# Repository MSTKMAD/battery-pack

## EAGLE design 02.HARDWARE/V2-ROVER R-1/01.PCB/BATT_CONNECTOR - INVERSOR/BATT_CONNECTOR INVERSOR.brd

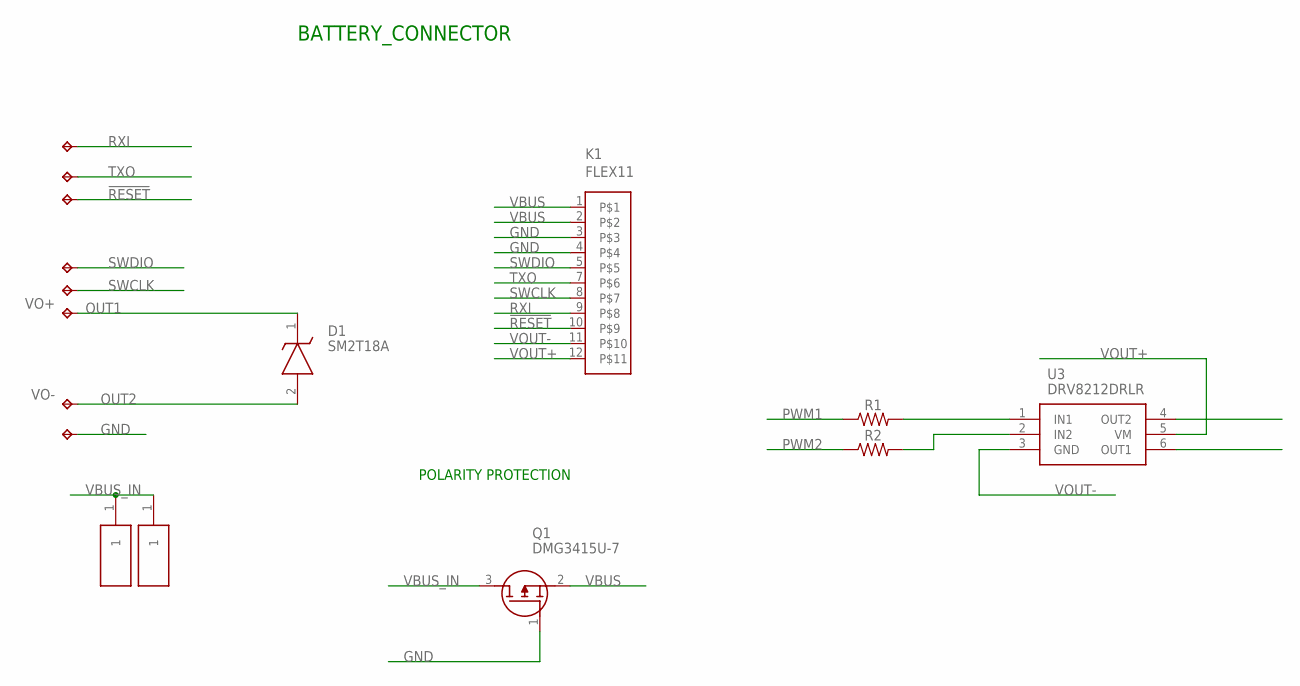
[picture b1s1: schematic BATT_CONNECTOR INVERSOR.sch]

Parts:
!RESET: TPB2,54; B2,54
D1: SM2T18A
GND: TPB2,54; B2,54
H1, H2: S1761-42R; S176142R
K1: FLEX11
Q1: DMG3415U-7; SSM3J332RLFT
R1, R2: 0805
RXI: TPB2,54; B2,54
SWCLK: TPB2,54; B2,54
SWDIO: TPB2,54; B2,54
TXO: TPB2,54; B2,54
U3: DRV8212DRLR; SOTFL50P160X60-6N
VO+: TPB2,54; B2,54
VO-: TPB2,54; B2,54

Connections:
!RESET: !RESET.TP, K1.10
GND: GND.TP, K1.3, K1.4, Q1.1 (G)
unnamed: R1.2, U3.1 (IN1)
unnamed: R2.2, U3.2 (IN2)
OUT1: D1.1 (K), U3.6 (OUT1), VO+.TP
OUT2: D1.2 (A), U3.4 (OUT2), VO-.TP
PWM1: R1.1
PWM2: R2.1
RXI: K1.9, RXI.TP
SWCLK: K1.8, SWCLK.TP
SWDIO: K1.5, SWDIO.TP
TXO: K1.7, TXO.TP
VBUS: K1.1, K1.2, Q1.2 (S)
VBUS_IN: H1.1, H2.1, Q1.3 (D)
VOUT+: K1.12, U3.5 (VM)
VOUT-: K1.11, U3.3 (GND)

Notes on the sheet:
POLARITY PROTECTION
BATTERY_CONNECTOR

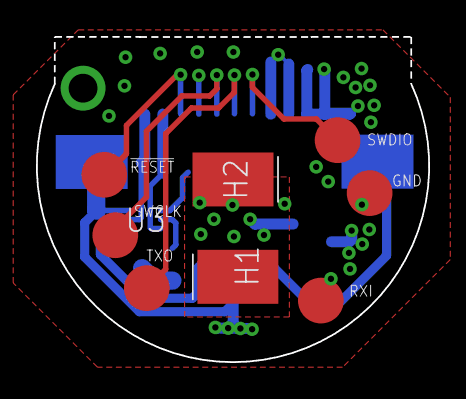
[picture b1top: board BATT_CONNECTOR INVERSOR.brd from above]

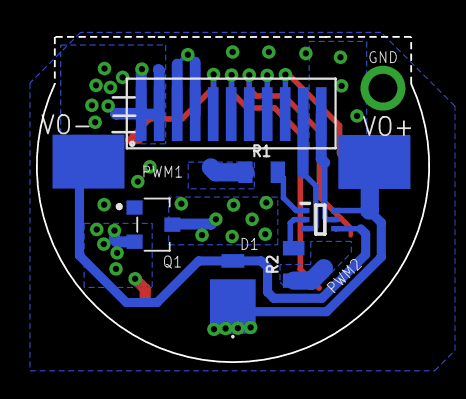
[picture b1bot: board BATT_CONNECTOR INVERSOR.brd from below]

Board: 4 copper layers, 21.8 x 18.1 mm, 16 parts (8 on the bottom side), 14 nets.

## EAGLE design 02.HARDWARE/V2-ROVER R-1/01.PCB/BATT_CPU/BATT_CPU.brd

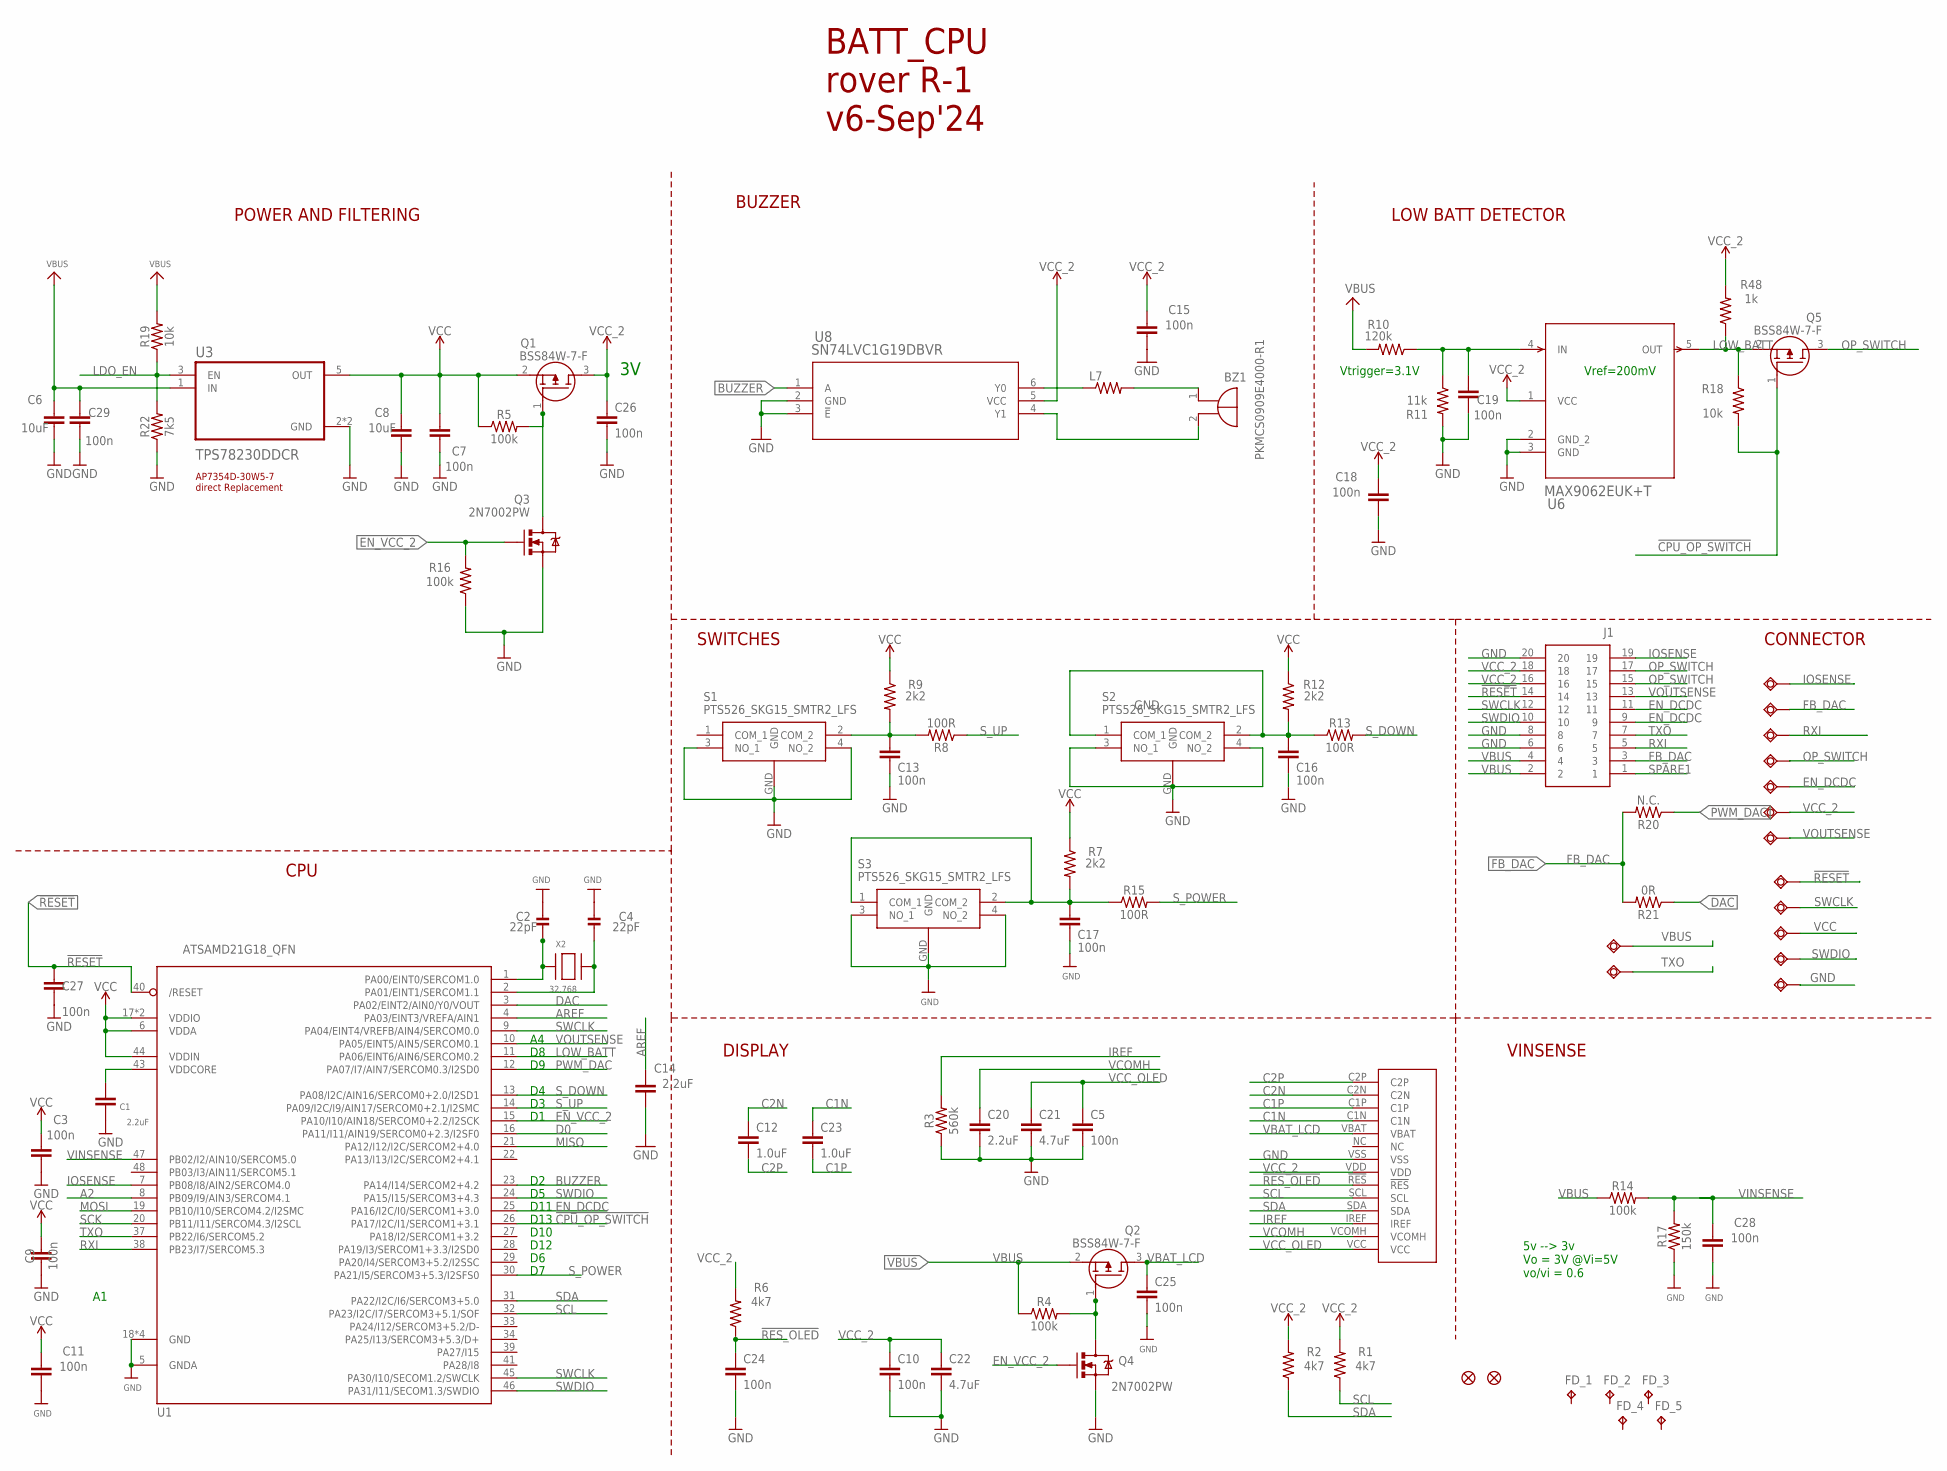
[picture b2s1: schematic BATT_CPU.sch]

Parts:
BZ1: PKMCS0909E4000-R1; PKMCS0909
C1, C14, C20: 2.2uF; 0603
C2, C4: 22pF; 0603-NO
C3, C5, C7, C9, C10, C11, C13, C15, C16, C17, C18, C19, C24, C25, C26, C27, C28, C29: 100n; 0402
C6, C8: 10uF; 0603
C12, C23: 1.0uF; 0402
C21, C22: 4.7uF; 0603
EN_DCDC: TESTPAD_TPSQB1,27; TESTPAD_B1,27
FB_DAC: TESTPAD_TPSQB1,27; TESTPAD_B1,27
FD_1, FD_2, FD_3, FD_4, FD_5: FD_1; TP06SQ
IOSENSE: TESTPAD_TPSQB1,27; TESTPAD_B1,27
J1: DF40C_2.0_-20DS-0.4V_51_; DF40C2020DS04V51
L7: MMZ2012Y202BT000; 0805
OP_SWITCH: TESTPAD_TPSQB1,27; TESTPAD_B1,27
Q1, Q2, Q5: BSS84W-7-F; SOT65P222X110-3N
Q3, Q4: 2N7002PW; SOT323
R1, R2, R6: 4k7; 0402
R3: 560k; 0402
R4, R5, R14, R16: 100k; 0402
R7, R9, R12: 2k2; 0402
R8, R13, R15: 100R; 0402
R10: 120k; 0402
R11: 11k; 0402
R17: 150k; 0402
R18, R19: 10k; 0402
R20: N.C.; 0402
R21: 0R; 0402
R22: 7k5; 0402
R48: 1k; 0402
RXI: TESTPAD_TPSQB1,27; TESTPAD_B1,27
S1, S2, S3: PTS526_SKG15_SMTR2_LFS; PTS526SKG15SMTR2LFS
U1: ATSAMD21G18_QFN; TQFN48_7MM
U3: TPS78230DDCR; SOT95P280X110-5N
U6: MAX9062EUK+T; 21-0057F_MXM
U8: SN74LVC1G19DBVR; DBV6
U$30: 64X32_OLED_049; LCD_14_PINS
U$34, U$35: FIDUCIAL""; FIDUCIAL_1MM
VBUS, VBUS1, VBUS2, VBUS3, VBUS4, VBUS5, VBUS6: TESTPAD_TPSQB1,27; TESTPAD_B1,27
VCC_2: TESTPAD_TPSQB1,27; TESTPAD_B1,27
VOUTSENSE: TESTPAD_TPSQB1,27; TESTPAD_B1,27
X2: 32.768; XTAL3215

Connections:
!CPU_OP_SWITCH: Q5.1 (G), R18.2, U1.26 (PA17/I2C/I1/SERCOM1+3.1)
!RESET: C27.1, J1.14, U1.40 (/RESET), VBUS1.TP
!RES_OLED: C24.1, R6.1, U$30.!RES
A2: U1.8 (PB09/I9/AIN3/SERCOM4.1)
AREF: C14.1, U1.4 (PA03/EINT3/VREFA/AIN1)
BUZZER: U1.23 (PA14/I14/SERCOM2+4.2), U8.1 (A)
C1N: C23.1, U$30.C1N
C1P: C23.2, U$30.C1P
C2N: C12.1, U$30.C2N
C2P: C12.2, U$30.C2P
D0: U1.16 (PA11/I11/AIN19/SERCOM0+2.3/I2SF0)
DAC: R21.1, U1.3 (PA02/EINT2/AIN0/Y0/VOUT)
EN_DCDC: EN_DCDC.TP, J1.9, J1.11, U1.25 (PA16/I2C/I0/SERCOM1+3.0)
EN_VCC_2: Q3.1 (G), Q4.1 (G), R16.2, U1.15 (PA10/I10/AIN18/SERCOM0+2.2/I2SCK)
FB_DAC: FB_DAC.TP, J1.3, R20.2, R21.2
GND: C1.2, C2.2, C3.2, C4.2, C5.2, C6.2, C7.2, C8.2, C9.2, C10.2, C11.2, C13.2, C14.2, C15.2, C16.2, C17.2, C18.2, C19.2, C20.2, C21.2, C22.2, C24.2, C25.2, C26.2, C27.2, C28.2, C29.2, J1.6, J1.8, J1.20, Q3.2 (S), Q4.2 (S), R3.1, R11.2, R16.1, R17.1, R22.1, S1.3 (NO_1), S1.4 (NO_2), S1.GND, S2.3 (NO_1), S2.4 (NO_2), S2.GND, S3.3 (NO_1), S3.4 (NO_2), S3.GND, U1.5 (GNDA), U1.18 (GND), U1.35 (GND), U1.42 (GND), U1.THERMAL (GND), U3.2 (GND), U3.4 (GND), U6.2 (GND_2), U6.3 (GND), U8.2 (GND), U8.3 (!E), U$30.VSS, VBUS4.TP
IOSENSE: IOSENSE.TP, J1.19, U1.7 (PB08/I8/AIN2/SERCOM4.0)
IREF: R3.2, U$30.IREF
LDO_EN: R19.1, R22.2, U3.3 (EN)
LOW_BATT: Q5.2 (S), R18.1, R48.1, U1.11 (PA06/EINT6/AIN6/SERCOM0.2), U6.5 (OUT)
MISO: U1.21 (PA12/I12/I2C/SERCOM2+4.0)
MOSI: U1.19 (PB10/I10/SERCOM4.2/I2SMC)
unnamed: C17.1, R7.2, R15.1, S3.1 (COM_1), S3.2 (COM_2)
unnamed: C13.1, R8.2, R9.2, S1.2 (COM_2)
unnamed: C16.1, R12.2, R13.1, S2.1 (COM_1), S2.2 (COM_2)
unnamed: Q2.1 (G), Q4.3 (D), R4.2
unnamed: C2.1, U1.1 (PA00/EINT0/SERCOM1.0), X2.P$1
unnamed: Q1.1 (G), Q3.3 (D), R5.2
unnamed: C4.1, U1.2 (PA01/EINT1/SERCOM1.1), X2.P$2
unnamed: C19.1, R10.1, R11.1, U6.4 (IN)
unnamed: L7.1, U8.6 (Y0)
unnamed: BZ1.1 (+), L7.2
unnamed: BZ1.2 (-), U8.4 (Y1)
OP_SWITCH: J1.15, J1.17, OP_SWITCH.TP, Q5.3 (D)
PWM_DAC: R20.1, U1.12 (PA07/I7/AIN7/SERCOM0.3/I2SD0)
RXI: J1.5, RXI.TP, U1.38 (PB23/I7/SERCOM5.3)
SCK: U1.20 (PB11/I11/SERCOM4.3/I2SCL)
SCL: R1.1, U1.32 (PA23/I2C/I7/SERCOM3+5.1/SOF), U$30.SCL
SDA: R2.1, U1.31 (PA22/I2C/I6/SERCOM3+5.0), U$30.SDA
SPARE1: J1.1
SWDIO: J1.10, U1.24 (PA15/I15/SERCOM3+4.3), U1.46 (PA31/I11/SECOM1.3/SWDIO), VBUS3.TP
S_DOWN: R13.2, U1.13 (PA08/I2C/AIN16/SERCOM0+2.0/I2SD1)
S_POWER: R15.2, U1.30 (PA21/I5/SERCOM3+5.3/I2SFS0)
S_UP: R8.1, U1.14 (PA09/I2C/I9/AIN17/SERCOM0+2.1/I2SMC)
TXO: J1.7, U1.37 (PB22/I6/SERCOM5.2), VBUS6.TP
VBAT_LCD: C25.1, Q2.3 (D), U$30.VBAT
VBUS: C6.1, C29.1, J1.2, J1.4, Q2.2 (S), R4.1, R10.2, R14.1, R19.2, U3.1 (IN), VBUS5.TP
VCC: C3.1, C7.1, C8.1, C9.1, C11.1, Q1.2 (S), R5.1, R7.1, R9.1, R12.1, R48.2, U1.6 (VDDA), U1.17 (VDDIO), U1.36 (VDDIO), U1.44 (VDDIN), U3.5 (OUT), VBUS.TP
VCC_2: C10.1, C15.1, C18.1, C22.1, C26.1, J1.16, J1.18, Q1.3 (D), R1.2, R2.2, R6.2, U6.1 (VCC), U8.5 (VCC), U$30.VDD, VCC_2.TP
VCC_OLED: C5.1, C21.1, U$30.VCC
VCOMH: C20.1, U$30.VCOMH
VDDCORE: C1.1, U1.43 (VDDCORE)
VINSENSE: C28.1, R14.2, R17.2, U1.47 (PB02/I2/AIN10/SERCOM5.0)
VOUTSENSE: J1.13, U1.10 (PA05/EINT5/AIN5/SERCOM0.1), VOUTSENSE.TP

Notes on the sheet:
POWER AND FILTERING
BUZZER
AP7354D-30W5-7 direct Replacement
D10
LOW BATT DETECTOR
CPU
Vref=200mV
Vtrigger=3.1V
D13
D11
D12
5v --> 3v Vo = 3V @Vi=5V vo/vi = 0.6
BATT_CPU rover R-1 v6-Sep'24
DISPLAY
SWITCHES
CONNECTOR
VINSENSE

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
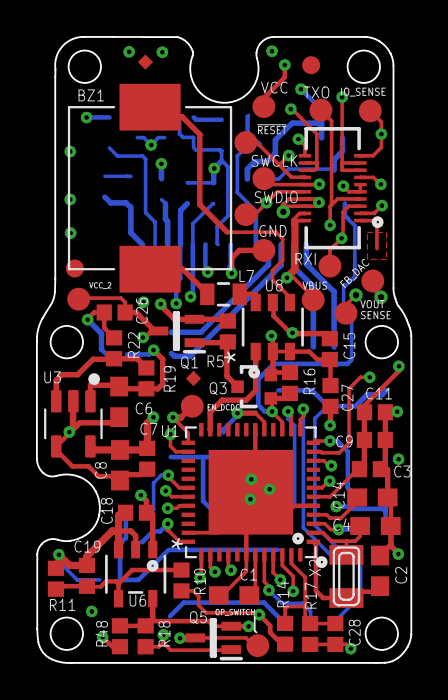
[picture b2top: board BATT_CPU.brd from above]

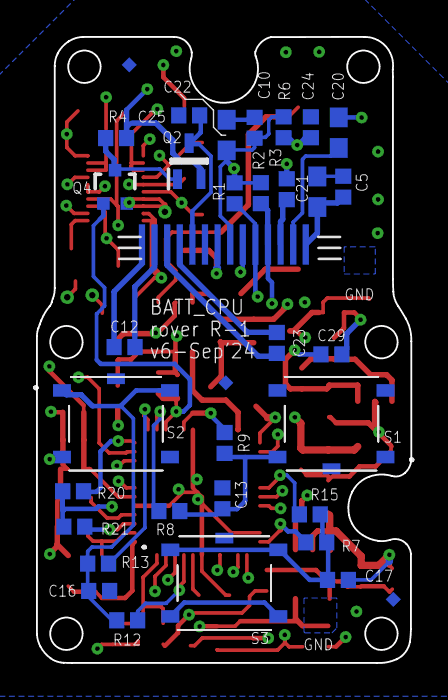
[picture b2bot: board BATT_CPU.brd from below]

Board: 4 copper layers, 20.8 x 34.8 mm, 90 parts (35 on the bottom side), 49 nets.

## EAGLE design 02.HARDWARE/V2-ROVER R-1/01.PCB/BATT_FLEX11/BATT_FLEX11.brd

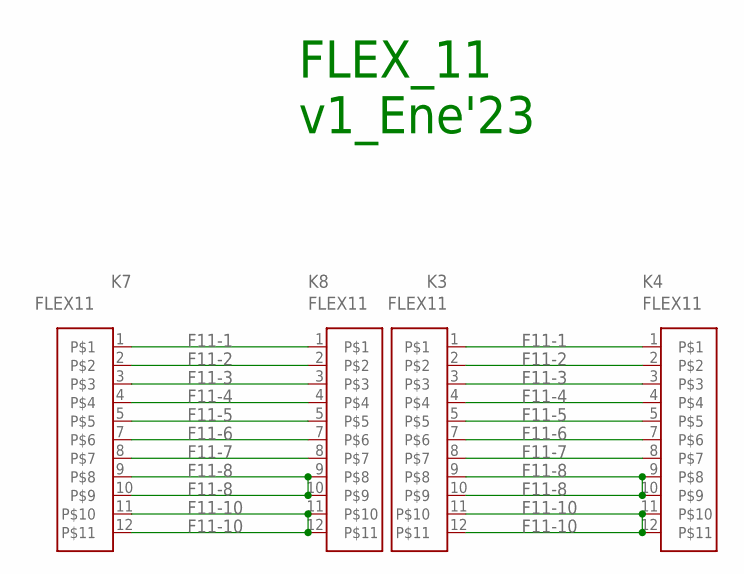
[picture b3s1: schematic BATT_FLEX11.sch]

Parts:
K3, K4, K7, K8: FLEX11

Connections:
F11-1: K3.1, K4.1, K7.1, K8.1
F11-2: K3.2, K4.2, K7.2, K8.2
F11-3: K3.3, K4.3, K7.3, K8.3
F11-4: K3.4, K4.4, K7.4, K8.4
F11-5: K3.5, K4.5, K7.5, K8.5
F11-6: K3.7, K4.7, K7.7, K8.7
F11-7: K3.8, K4.8, K7.8, K8.8
F11-8: K3.9, K3.10, K4.9, K4.10, K7.9, K7.10, K8.9, K8.10
F11-10: K3.11, K3.12, K4.11, K4.12, K7.11, K7.12, K8.11, K8.12

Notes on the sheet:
FLEX_11 v1_Ene'23

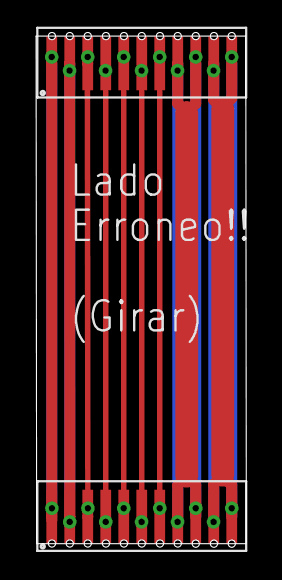
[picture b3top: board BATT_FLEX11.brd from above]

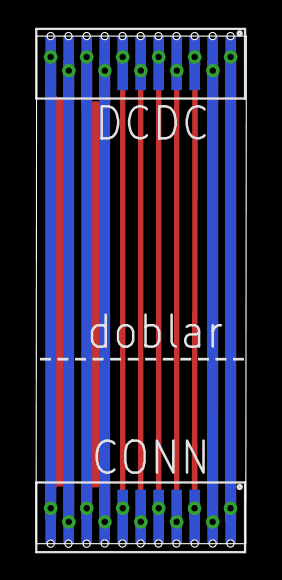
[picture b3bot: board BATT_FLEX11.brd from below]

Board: 2 copper layers, 11.7 x 28.2 mm, 4 parts (2 on the bottom side), 9 nets.

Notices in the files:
parts and their libraries:
SparkFun-Resistors: Licensing: Creative Commons ShareAlike 4.0 International - https://creativecommons.org/licenses/by-sa/4.0
microbuilder: This work is placed in the public domain, and may be freely used for commercial and non-commercial work with the following conditions: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
